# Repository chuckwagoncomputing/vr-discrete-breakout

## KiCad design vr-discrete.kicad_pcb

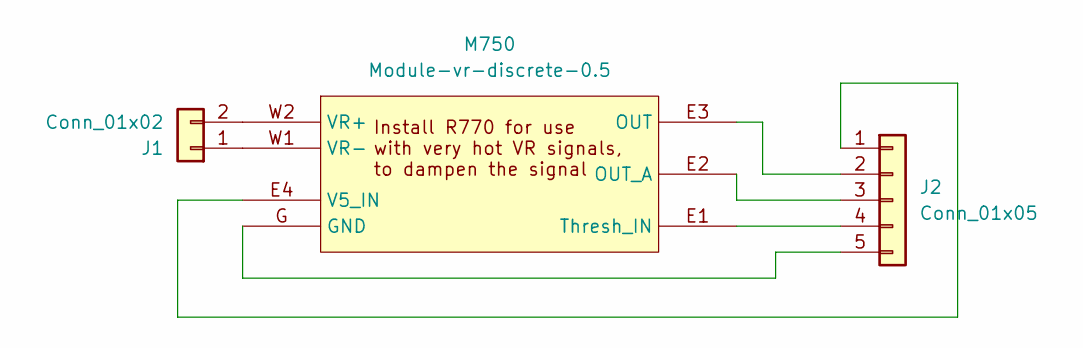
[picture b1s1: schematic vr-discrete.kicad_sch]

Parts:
J1: Conn_01x02; PinHeader_1x02_P2.54mm_Vertical
J2: Conn_01x05; PinHeader_1x05_P2.54mm_Vertical
M750: Module-vr-discrete-0.5; vr-discrete

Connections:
unnamed: J1.1, M750.W1 (VR-)
unnamed: J1.2, M750.W2 (VR+)
unnamed: J2.1, M750.E4 (V5_IN)
unnamed: J2.2, M750.E3 (OUT)
unnamed: J2.3, M750.E2 (OUT_A)
unnamed: J2.4, M750.E1 (Thresh_IN)
unnamed: J2.5, M750.G (GND)

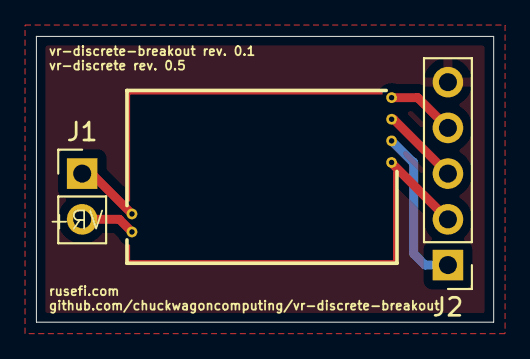
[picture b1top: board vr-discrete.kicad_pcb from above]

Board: 2 copper layers, 25.4 x 15.9 mm, 3 parts (0 on the bottom side), 7 nets.

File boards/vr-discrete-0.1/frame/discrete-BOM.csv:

Comment,Designator,Footprint,LCSC Part #
"Conn_01x02","J1","PinHeader_1x02_P2.54mm_Vertical",""
"Conn_01x05","J2","PinHeader_1x05_P2.54mm_Vertical",""
"Module:vr-discrete/0.5","M750","vr-discrete",""

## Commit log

2024-04-12 use branch with kicad 8
2024-04-12 add info to revision.txt
2024-04-13 Add schematic
2024-04-13 Add board
2024-04-13 add empty BOM
2024-04-13 [skip actions] Auto-generated board v2.1
2024-04-13 GHA says update hellen-one
2024-04-21 empty readme
2024-04-22 replace components
2024-05-18 GHA says update kicad6-libraries
